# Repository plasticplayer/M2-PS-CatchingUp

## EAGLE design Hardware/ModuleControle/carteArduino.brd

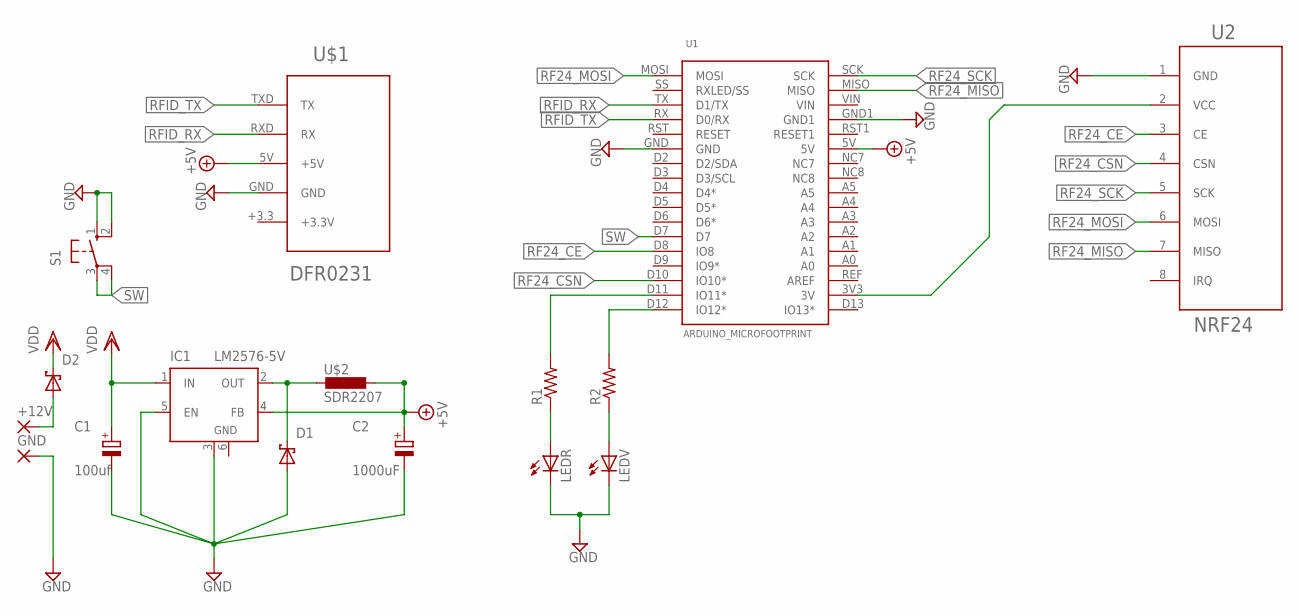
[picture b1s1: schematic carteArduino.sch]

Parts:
+12V: 3,81/1,4
C1: 100uf; PANASONIC_E
C2: 1000uF; PANASONIC_G
D1, D2: SCHOTTKY-DIODESMC; SMC
GND: 3,81/1,4
IC1: LM2576-5V; TO263-5
LEDR: LED3MM
LEDV: LED3MM
R1, R2: R-US_R1206; R1206
S1: 40-XX; B3F-40XX
U1: ARDUINO_MICROFOOTPRINT; ARDUINO-MICRO
U2: NRF24; NRF_24_8PIN
U$1: DFR0231; DFR0231_5PIN_HOLES
U$2: SDR2207; SM

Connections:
+5V: C2.+, IC1.4 (FB), U1.5V, U$1.5V (+5V), U$2.P$2 (2)
GND: C1.-, C2.-, D1.A, GND.1, IC1.3 (GND), IC1.5 (EN), IC1.6 (GND), LEDR.K (C), LEDV.K (C), S1.1 (S), S1.2 (S1), U1.GND, U1.GND1, U2.1 (GND), U$1.GND
unnamed: LEDR.A, R1.1
unnamed: LEDV.A, R2.1
unnamed: D1.C, IC1.2 (OUT), U$2.P$1 (1)
unnamed: R2.2, U1.D12 (IO12*)
unnamed: R1.2, U1.D11 (IO11*)
unnamed: +12V.1, D2.A
unnamed: U1.3V3 (3V), U2.2 (VCC)
RF24_CE: U1.D8 (IO8), U2.3 (CE)
RF24_CSN: U1.D10 (IO10*), U2.4 (CSN)
RF24_MISO: U1.MISO, U2.7 (MISO)
RF24_MOSI: U1.MOSI, U2.6 (MOSI)
RF24_SCK: U1.SCK, U2.5 (SCK)
RFID_RX: U1.TX (D1/TX), U$1.RXD (RX)
RFID_TX: U1.RX (D0/RX), U$1.TXD (TX)
SW: S1.3, S1.4 (P1), U1.D7
VDD: C1.+, D2.C, IC1.1 (IN)

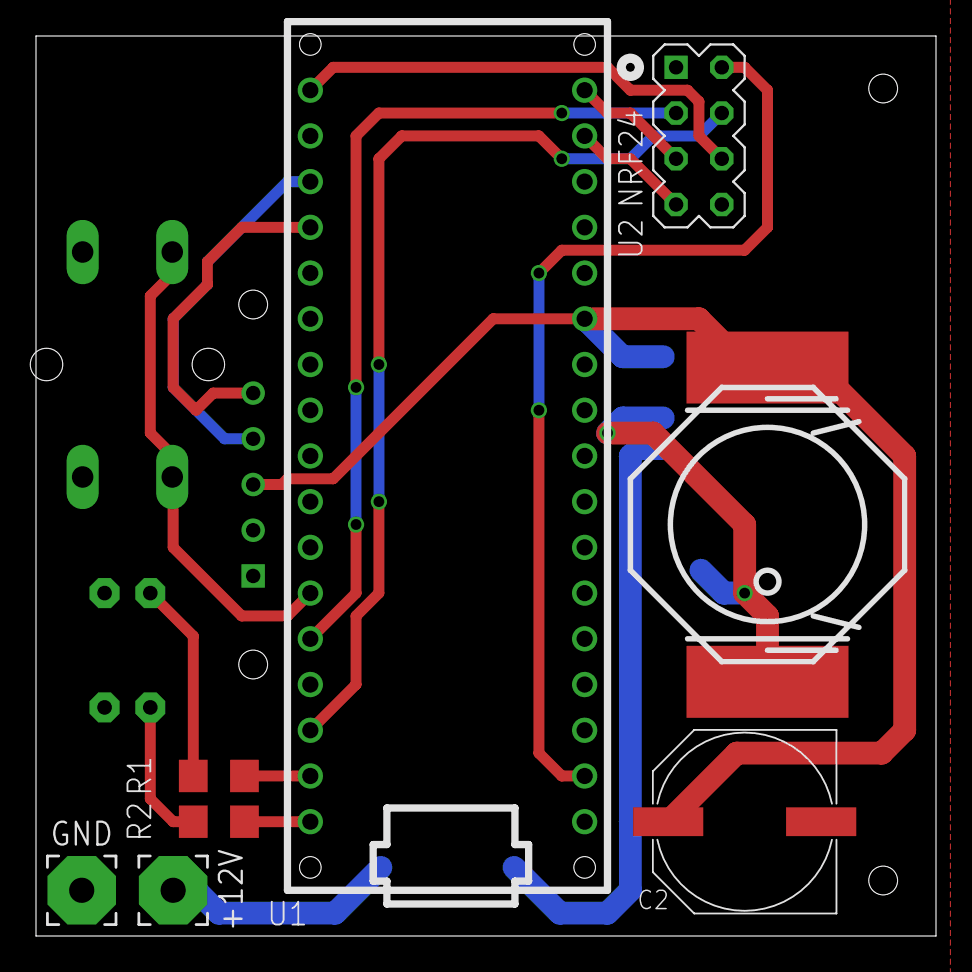
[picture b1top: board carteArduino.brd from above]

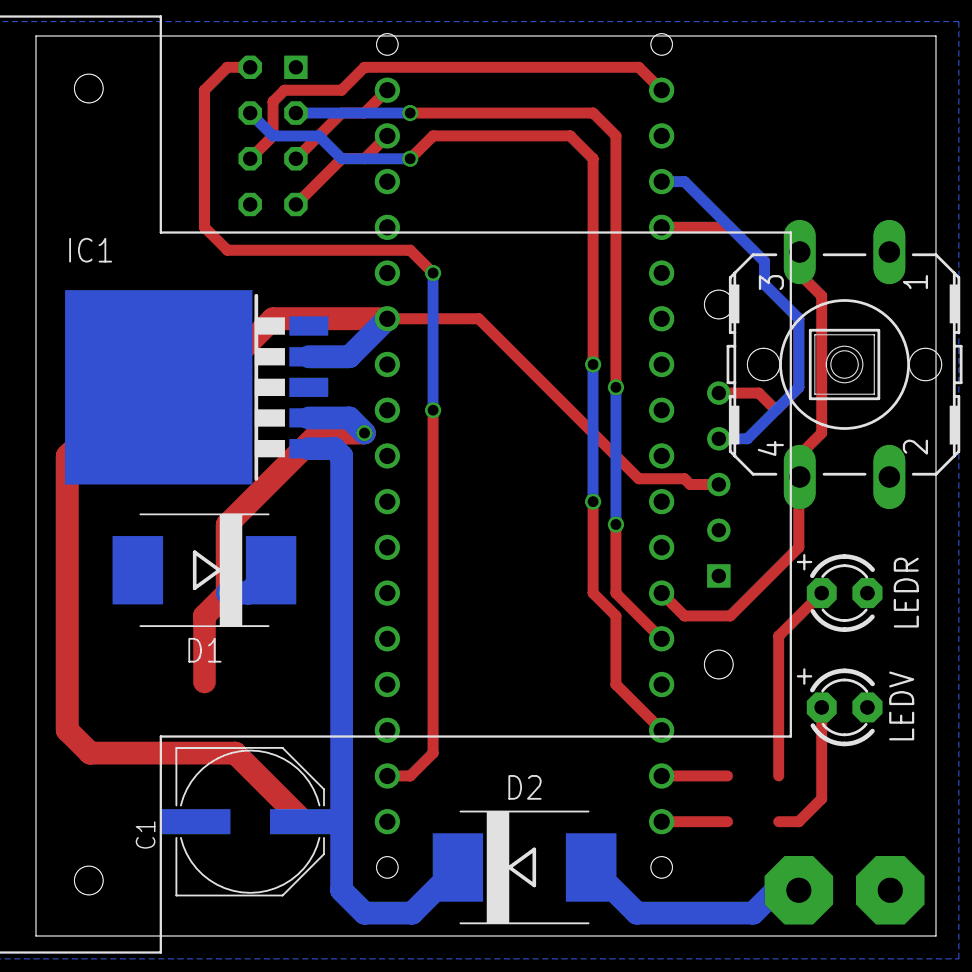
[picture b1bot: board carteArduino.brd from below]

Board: 2 copper layers, 50.0 x 50.0 mm, 16 parts (8 on the bottom side), 18 nets.

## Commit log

2015-02-05 ModuleEnregistrement - Communication - ADD
    Création protocol communication
    Ajout communication NRF
2015-02-05 Init Git Repository
2015-02-08 Module Controle
2015-02-10 Change
2015-02-10 Fix Makefile
2015-02-11 Presque fonctionnel
2015-02-11 Implémentation Keep Alive + changement protocol
    Voir le document pour les modification du protocole
    A=>R = nodata
    R=>A status Enregistrement:
    0x00 = En attente
    0x01 = En enregistrement
2015-02-15 correction bug envoi status en parking
2015-02-18 Implementation keepAlive + Correctif protocol
2015-02-19 Correction BUG LED module activation
2015-02-19 GitIgnore
2015-02-19 Module Recording Acquisition image
2015-02-26 Removing Useless preview for capture
2015-02-26 Only recording images
2015-02-26 Using Thread to grab the images
2015-03-04 Correctif Bug + Fichier configuration
2015-03-04 Moving Folder
2015-03-05 Adding Logger And cleaning Code
2015-03-05 Git version now used to print on start
2015-03-06 Add ability to take a snapshoot and save it to ram => used to send it over the network For the moment it uses a temporary file
2015-03-13 Création serveur - Couche Udp + Recorder
2015-03-13 Creation Couche Udp Module Enregistreur
2015-03-19 Modularising Module and adding macros to LOG
2015-03-19 Update Makefile
2015-03-26 Add RPI UDP AND UPDATE UDP SERVER
    Error on RPI.UDP.SEND functions ==> Seg fault
2015-03-27 Mergin project together Adding details in logger Switching all standard output to Logger
2015-04-01 Moving to split folder
2015-04-01 Adding Software
2015-04-21 Correct Udp Server and Client
    Re-implement Udp Client: Auto resend Image parts not receive
2015-04-29 Integration Rpi and Server
2015-04-30 Verify and correct integration
2015-04-30 Clean Makefile
2015-05-04 Adding H.264 webcam recording Cleanning Makefile Cleanning Warnings
2015-05-04 Update makefile to uses dependencies compiling Update gitignore to remove depend folder
2015-05-04 Recording done from the console Adding soft to control the servo
2015-05-04 Add Mysql Functions
2015-05-04 Correct Header Communication
2015-05-04 Recording the webcam + the sound + snapshots
2015-05-05 Adding Traking (FPS drop to ~10) Need to make a thread Using class to store image from webcam Sound recording is disabled for the moment because the microphone conflicts with the webcam sometimes
2015-05-06 Update ModuleActivation (fix leak ?)
2015-05-07 Bkp bug act
2015-05-07 Revert "Adding Traking (FPS drop to ~10) Need to make a thread"
    This reverts commit 5965916f474f73542e1370a07f0f7235d3fddab9.
2015-05-07 Correct FTP Server - Works
2015-05-07 Correct FTP Server
2015-05-10 modification des fenetres room ajout/modification intervenant (finies) + modifications mineures d'autres fenêtres
2015-05-10 Adding HardWare
2015-05-11 Server Ftp : Add one Time Password + Add Mysql Files Functions
2015-05-11 Module Enregistrement Add One Time Password
2015-05-13 Correct merge loss traitement
2015-05-13 Correct Merge And SSL Client
2015-05-13 FIX SSL - Remove SHA - Include SQL
2015-05-18 Fix some warnings Prepare for multithread Image Processing
2015-05-18 Update logger to be threaded and threadsafe
2015-05-18 Create administration Function Card - Users - Room
2015-05-18 Fix bad socket client and port for testing
2015-05-19 Change exec context to folder of the binary file
2015-05-19 Correct AppliAdmin Protocol - Add Mysql Try/Catch
2015-05-20 Update For 3D Printer
2015-05-20 mise à jour speaker update, card creation, room creation, speaker creation, calendar et configuration
2015-05-20 idem precedent commit
2015-05-20 Primitive tracking OK
2015-05-21 Update Server Communication - Appli Config
2015-05-21 Add Client Communication - Config Appli
2015-05-21 Running the image processing under a other thread
2015-05-22 Before Abs value
2015-05-27 AppliConfig Add Recorder Functions
2015-05-27 Update AppliConf Server functions
2015-05-27 Fix NRF Parring Bug
2015-05-28 Update AppliConfig
2015-05-28 pouet
2015-05-28 add Logger
2015-05-28 add userlogin
2015-05-28 Integrate Communication functions
2015-05-28 Integration AppliConf Communication
2015-05-28 Update Communication Server
2015-06-03 Update Hardware
2015-06-03 Update gitignore
2015-06-04 Add ReaderCard Functions
2015-06-04 Create ModuleReader Code
2015-06-06 AppliConfig : Add Card reader. Correct UserLogin
2015-06-06 Update Card / Rooms IHM
2015-06-07 Correct Interface Speaker - Recorder
2015-06-07 Fix Bugs on Server
2015-06-08 Update image viewing now it's working ;)
2015-06-08 Update viewing of image
2015-06-08 Update image sending and add configuration params to flip image
2015-06-09 Fix Communication - Function not found
2015-06-10 Insert Log Pannel
2015-06-10 Correct Configuration Interface
2015-06-10 IHM - Add Reloads functions - And Refresh Thread for Recorders
2015-06-10 Correct Recorder display
2015-06-10 Add Website
2015-06-10 Update Server
2015-06-10 Fix raspi recording
2015-06-10 Update Website
2015-06-11 Fix Card creation
2015-06-11 Update application Switch to fullsreen available
2015-06-11 FIXIN
2015-06-11 Update windows and NRF id's
2015-06-11 Try Catch
2015-06-11 Correct Single acces MYSQL
2015-06-11 update
    Intégration des références (écriture, lecture)
2015-06-11 Fix logs
2015-06-11 Update For screen Shoots
2015-06-12 Mise à jour
    Mise à jour
2015-06-16 Update logger to threaded version
2015-06-16 Update Lo
2015-06-18 UpdateWebsite
2015-06-19 Add auto-reconnection functions
2015-06-23 Authentification
    Authentification
2015-06-24 On branch site Changes to be committed: (use "git reset HEAD <file>..." to unstage)
    modified: admin.php
2015-06-25 include Parser + Ftp logger
2015-06-26 Demo RPI
2015-06-26 The last Server Commit
2015-06-26 Remove Video
2015-06-26 Upate Config Application
    Correct First Creation
